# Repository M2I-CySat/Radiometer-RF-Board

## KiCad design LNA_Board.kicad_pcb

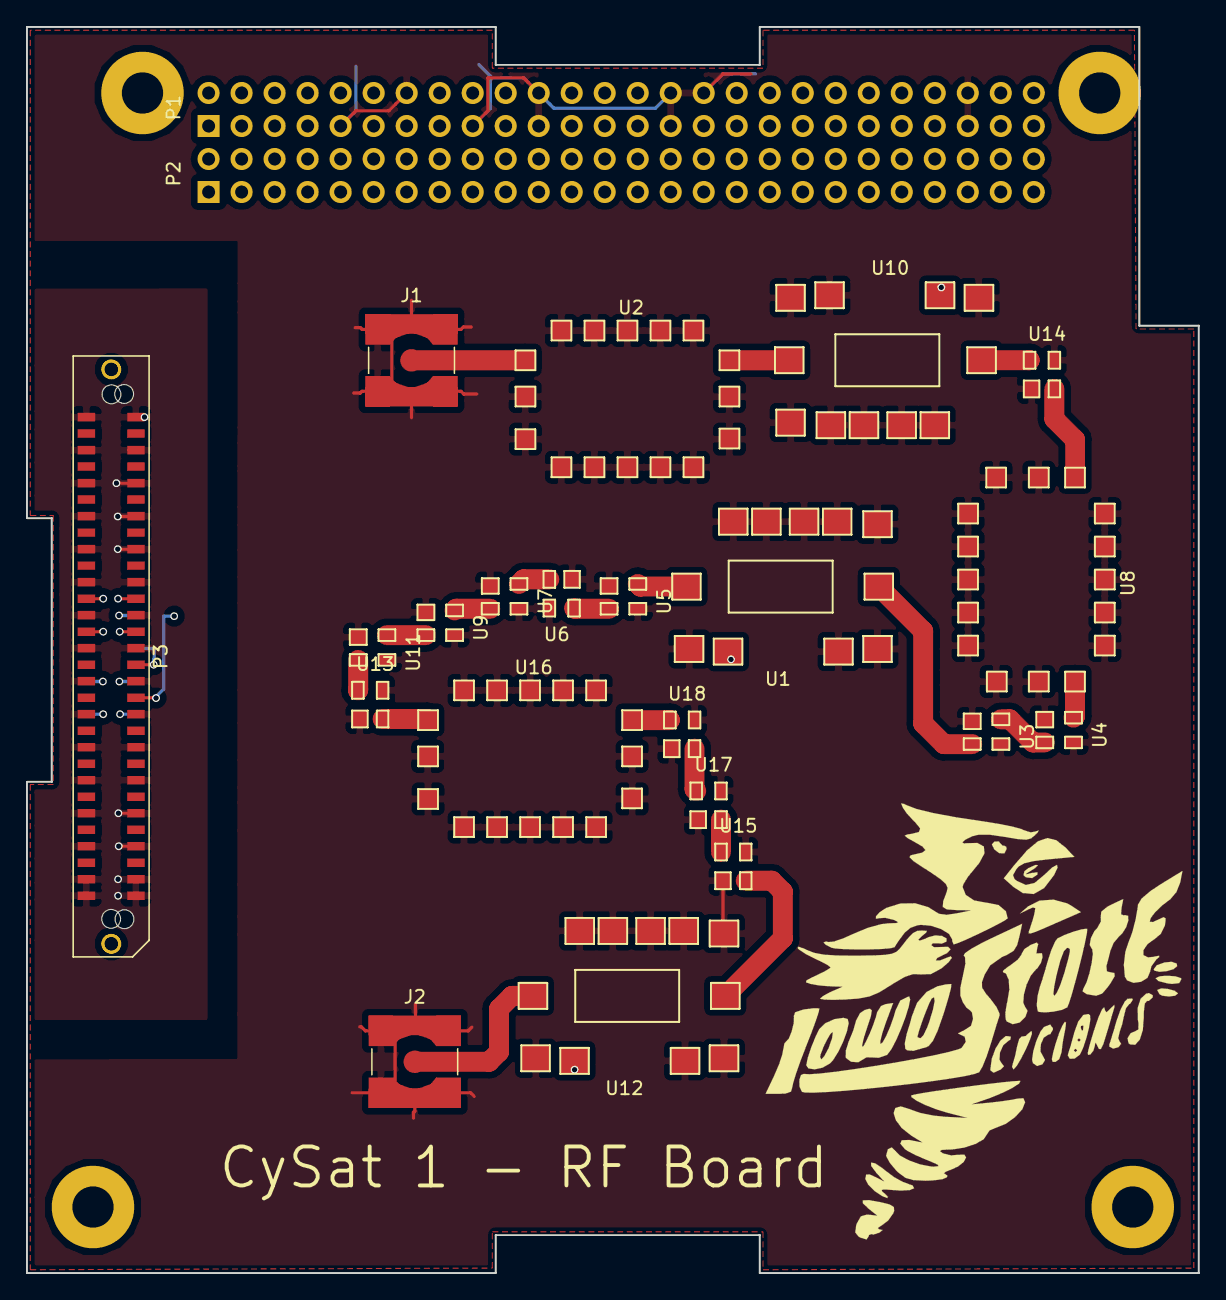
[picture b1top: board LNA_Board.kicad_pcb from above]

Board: 4 copper layers, 90.2 x 95.9 mm, 24 parts (1 on the bottom side), 45 nets.

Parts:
J1, J2: Conn_Coaxial; SMA_SMD_Jack_Straight
P1, P2: CONN_02X26; CSK_Header
P3, P3#2: CONN_02X30; MECF-30-01-NP-L-DV-WT_Socket
U1, U10, U12: TAMP_1512GLN+; TAMP-1512GLN+
U2, U8, U16: CBP-1400E+
U3, U4, U5, U6, U7, U9, U11, U13, U14, U15, U17, U18: LAT; LAT_1+

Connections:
+5V: P1.25, P1.26, P3.33, P3.34, P3.37, P3.38, P3#2.33, P3#2.34, P3#2.37, P3#2.38, U1.5, U10.5, U12.5
/SYS_SCL: P2.43, P3.25, P3#2.25
/SYS_SDA: P2.41, P3.29, P3#2.29
GND: J1.2, J2.2, P1.9, P1.14, P1.17, P1.21, P1.22, P1.29, P1.30, P1.32, P1.47, P1.48, P3.1, P3.2, P3.3, P3.4, P3.7, P3.8, P3.11, P3.12, P3.15, P3.16, P3.19, P3.20, P3.23, P3.24, P3.27, P3.28, P3.31, P3.32, P3.35, P3.36, P3.39, P3.40, P3.43, P3.44, P3.47, P3.48, P3.51, P3.52, P3.55, P3.56, P3.59, P3.60, P3#2.1, P3#2.2, P3#2.3, P3#2.4, P3#2.7, P3#2.8, P3#2.11, P3#2.12, P3#2.15, P3#2.16, P3#2.19, P3#2.20, P3#2.23, P3#2.24, P3#2.27, P3#2.28, P3#2.31, P3#2.32, P3#2.35, P3#2.36, P3#2.39, P3#2.40, P3#2.43, P3#2.44, P3#2.47, P3#2.48, P3#2.51, P3#2.52, P3#2.55, P3#2.56, P3#2.59, P3#2.60, U1.1, U1.3, U1.4, U1.6, U1.8, U1.9, U1.10, U1.11, U2.2, U2.3, U2.4, U2.5, U2.6, U2.7, U2.8, U2.9, U2.10, U2.12, U2.13, U2.14, U2.15, U2.16, U3.1, U3.3, U4.1, U4.3, U5.1, U5.3, U6.1, U6.3, U7.1, U7.3, U8.2, U8.3, U8.4, U8.5, U8.6, U8.7, U8.8, U8.9, U8.10, U8.12, U8.13, U8.14, U8.15, U8.16, U9.1, U9.3, U10.1, U10.3, U10.4, U10.6, U10.8, U10.9, U10.10, U10.11, U11.1, U11.3, U12.1, U12.3, U12.4, U12.6, U12.8, U12.9, U12.10, U12.11, U13.1, U13.3, U14.1, U14.3, U15.1, U15.3, U16.2, U16.3, U16.4, U16.5, U16.6, U16.7, U16.8, U16.9, U16.10, U16.12, U16.13, U16.14, U16.15, U16.16, U17.1, U17.3, U18.1, U18.3
unnamed: J1.1, U2.1
unnamed: J2.1, U12.7
unnamed: P3.5, P3#2.5
unnamed: P3.6, P3#2.6
unnamed: P3.9, P3#2.9
unnamed: P3.10, P3#2.10
unnamed: P3.13, P3#2.13
unnamed: P3.14, P3#2.14
unnamed: P3.17, P3#2.17
unnamed: P3.18, P3#2.18
unnamed: P3.21, P3#2.21
unnamed: P3.22, P3#2.22
unnamed: P3.26, P3#2.26
unnamed: P3.30, P3#2.30
unnamed: P3.41, P3#2.41
unnamed: P3.42, P3#2.42
unnamed: P3.45, P3#2.45
unnamed: P3.46, P3#2.46
unnamed: P3.49, P3#2.49
unnamed: P3.50, P3#2.50
unnamed: P3.53, P3#2.53
unnamed: P3.54, P3#2.54
unnamed: P3.57, P3#2.57
unnamed: P3.58, P3#2.58
unnamed: U1.2, U3.2
unnamed: U1.7, U5.4
unnamed: U3.4, U4.2
unnamed: U4.4, U8.11
unnamed: U5.2, U6.4
unnamed: U6.2, U7.4
unnamed: U7.2, U9.4
unnamed: U2.11, U10.2
unnamed: U10.7, U14.4
unnamed: U11.2, U13.4
unnamed: U9.2, U11.4
unnamed: U12.2, U15.2
unnamed: U13.2, U16.1
unnamed: U8.1, U14.2
unnamed: U15.4, U17.2
unnamed: U16.11, U18.4
unnamed: U17.4, U18.2

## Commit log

2018-07-28 Progress on board layout
2018-07-29 Tentative cardedge routing and gerbers
2018-07-30 Fixed soldermask
2018-07-31 Moved routing
2018-07-31 Changed trace width to match impediance
2018-08-02 Fixed traces
2019-10-29 Create fp-info-cache
2019-10-29 Project rename
    Renamed key files to better reflect what this board is, which is the LNA board for the SDR Radiometer.
